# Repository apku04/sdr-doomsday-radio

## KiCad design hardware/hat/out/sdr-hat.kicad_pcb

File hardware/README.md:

# KiCad boards in this folder

Reference only. The owner changed the design on 2026-10-26: the front panel is hand-wired (no panel PCB) and the owner designs the HAT. These scripted KiCad boards (ERC/DRC clean) are kept for reference.

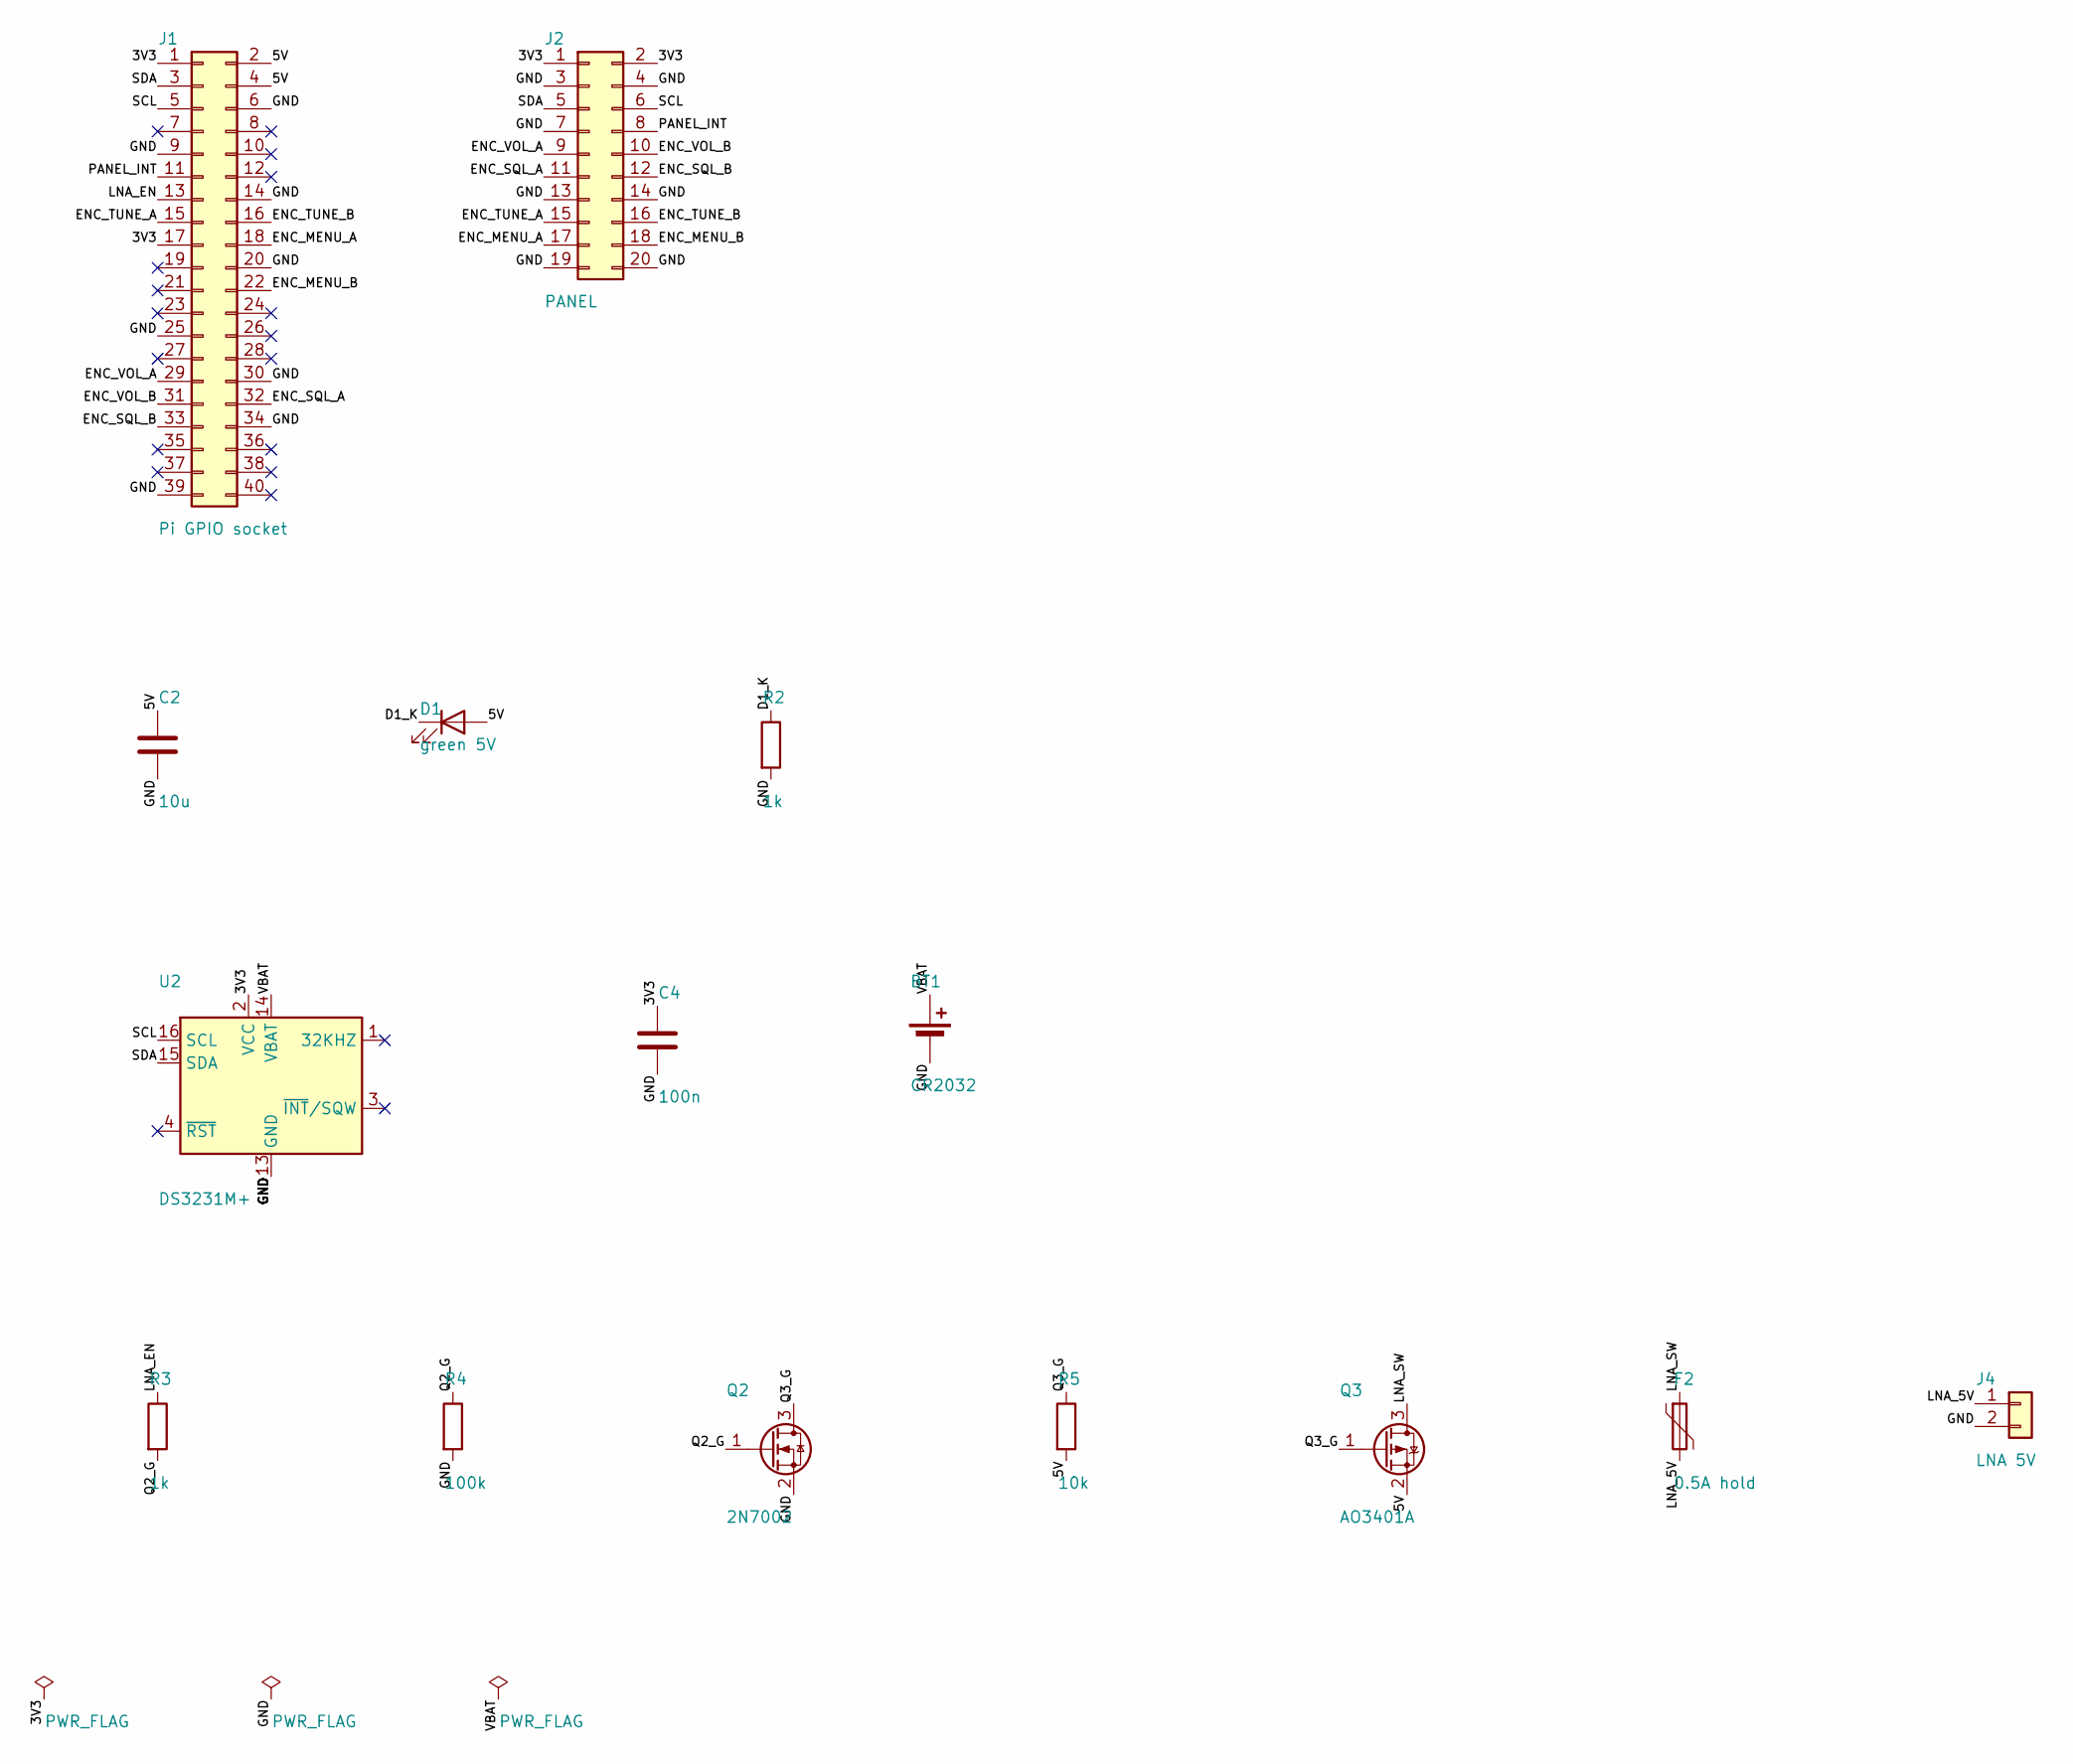
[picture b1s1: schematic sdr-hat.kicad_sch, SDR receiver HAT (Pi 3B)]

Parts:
BT1: CR2032; BatteryHolder_Keystone_3034_1x20mm
C2: 10u; C_0805_2012Metric
C4: 100n; C_0805_2012Metric
D1: green 5V; LED_0805_2012Metric
F2: 0.5A hold; Fuse_1206_3216Metric
J1: Pi GPIO socket; PinSocket_2x20_P2.54mm_Vertical
J2: PANEL; IDC-Header_2x10_P2.54mm_Vertical
J4: LNA 5V; JST_XH_B2B-XH-A_1x02_P2.50mm_Vertical
Q2: 2N7002; SOT-23
Q3: AO3401A; SOT-23
R2, R3: 1k; R_0805_2012Metric
R4: 100k; R_0805_2012Metric
R5: 10k; R_0805_2012Metric
U2: DS3231M+; SOIC-16W_7.5x10.3mm_P1.27mm

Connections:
3V3: C4.1, J1.1, J1.17, J2.1, J2.2, U2.2 (VCC)
5V: C2.1, D1.2 (A), J1.2, J1.4, Q3.2 (S), R5.2
D1_K: D1.1 (K), R2.1
ENC_MENU_A: J1.18, J2.17
ENC_MENU_B: J1.22, J2.18
ENC_SQL_A: J1.32, J2.11
ENC_SQL_B: J1.33, J2.12
ENC_TUNE_A: J1.15, J2.15
ENC_TUNE_B: J1.16, J2.16
ENC_VOL_A: J1.29, J2.9
ENC_VOL_B: J1.31, J2.10
GND: BT1.2 (-), C2.2, C4.2, J1.6, J1.9, J1.14, J1.20, J1.25, J1.30, J1.34, J1.39, J2.3, J2.4, J2.7, J2.13, J2.14, J2.19, J2.20, J4.2, Q2.2 (S), R2.2, R4.2, U2.5 (GND), U2.6 (GND), U2.7 (GND), U2.8 (GND), U2.9 (GND), U2.10 (GND), U2.11 (GND), U2.12 (GND), U2.13 (GND)
LNA_5V: F2.2, J4.1
LNA_EN: J1.13, R3.1
LNA_SW: F2.1, Q3.3 (D)
PANEL_INT: J1.11, J2.8
Q2_G: Q2.1 (G), R3.2, R4.1
Q3_G: Q2.3 (D), Q3.1 (G), R5.1
SCL: J1.5, J2.6, U2.16 (SCL)
SDA: J1.3, J2.5, U2.15 (SDA)
VBAT: BT1.1 (+), U2.14 (VBAT)

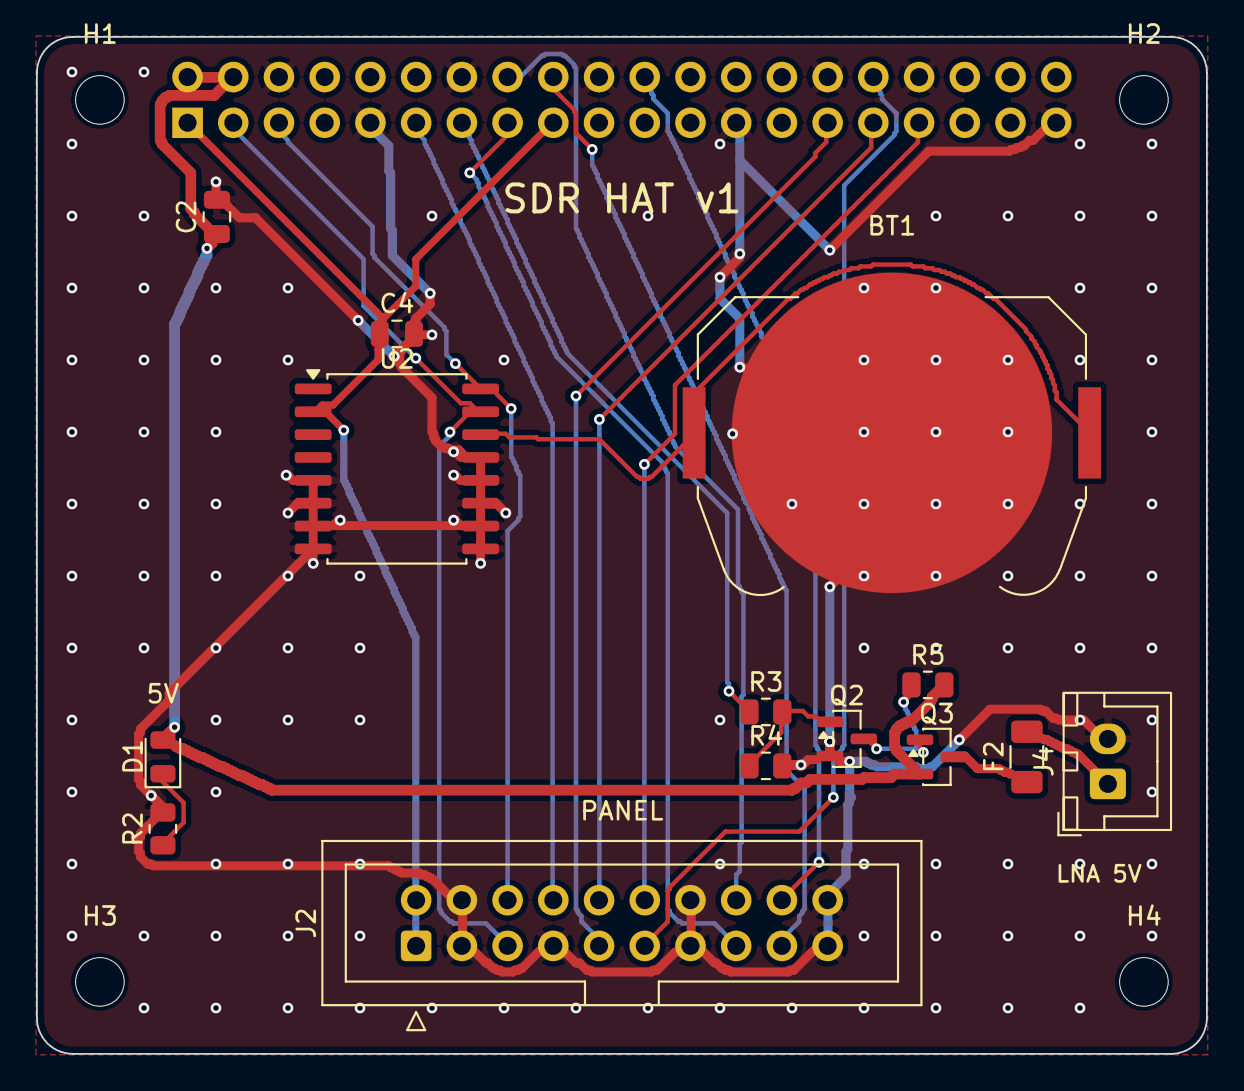
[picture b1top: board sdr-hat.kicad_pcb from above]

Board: 2 copper layers, 65.0 x 56.5 mm, 19 parts (1 on the bottom side), 21 nets.

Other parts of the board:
H1, H2, H3, H4: MountingHole_2.7mm_M2.5

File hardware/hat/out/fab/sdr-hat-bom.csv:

Qty,References,Value,Footprint,LCSC,Note
1,BT1,CR2032,BatteryHolder_Keystone_3034_1x20mm,,Keystone 3034 SMD holder
1,C2,10u,C_0805_2012Metric,,
1,C4,100n,C_0805_2012Metric,,
1,D1,green 5V,LED_0805_2012Metric,,
1,F2,0.5A hold,Fuse_1206_3216Metric,,PTC 1206 0.5 A hold
1,J1,Pi GPIO socket,PinSocket_2x20_P2.54mm_Vertical,,"2x20 female header, 8.5 mm (standard HAT height)"
1,J2,PANEL,IDC-Header_2x10_P2.54mm_Vertical,,"2x10 shrouded box header, keyed"
1,J4,LNA 5V,JST_XH_B2B-XH-A_1x02_P2.50mm_Vertical,,JST-XH 2-pin to back-panel LNA socket
1,Q2,2N7002,SOT-23,,
1,Q3,AO3401A,SOT-23,,
2,R2 R3,1k,R_0805_2012Metric,,
1,R4,100k,R_0805_2012Metric,,
1,R5,10k,R_0805_2012Metric,,
1,U2,DS3231M+,SOIC-16W_7.5x10.3mm_P1.27mm,,"I2C 0x68, MEMS RTC"

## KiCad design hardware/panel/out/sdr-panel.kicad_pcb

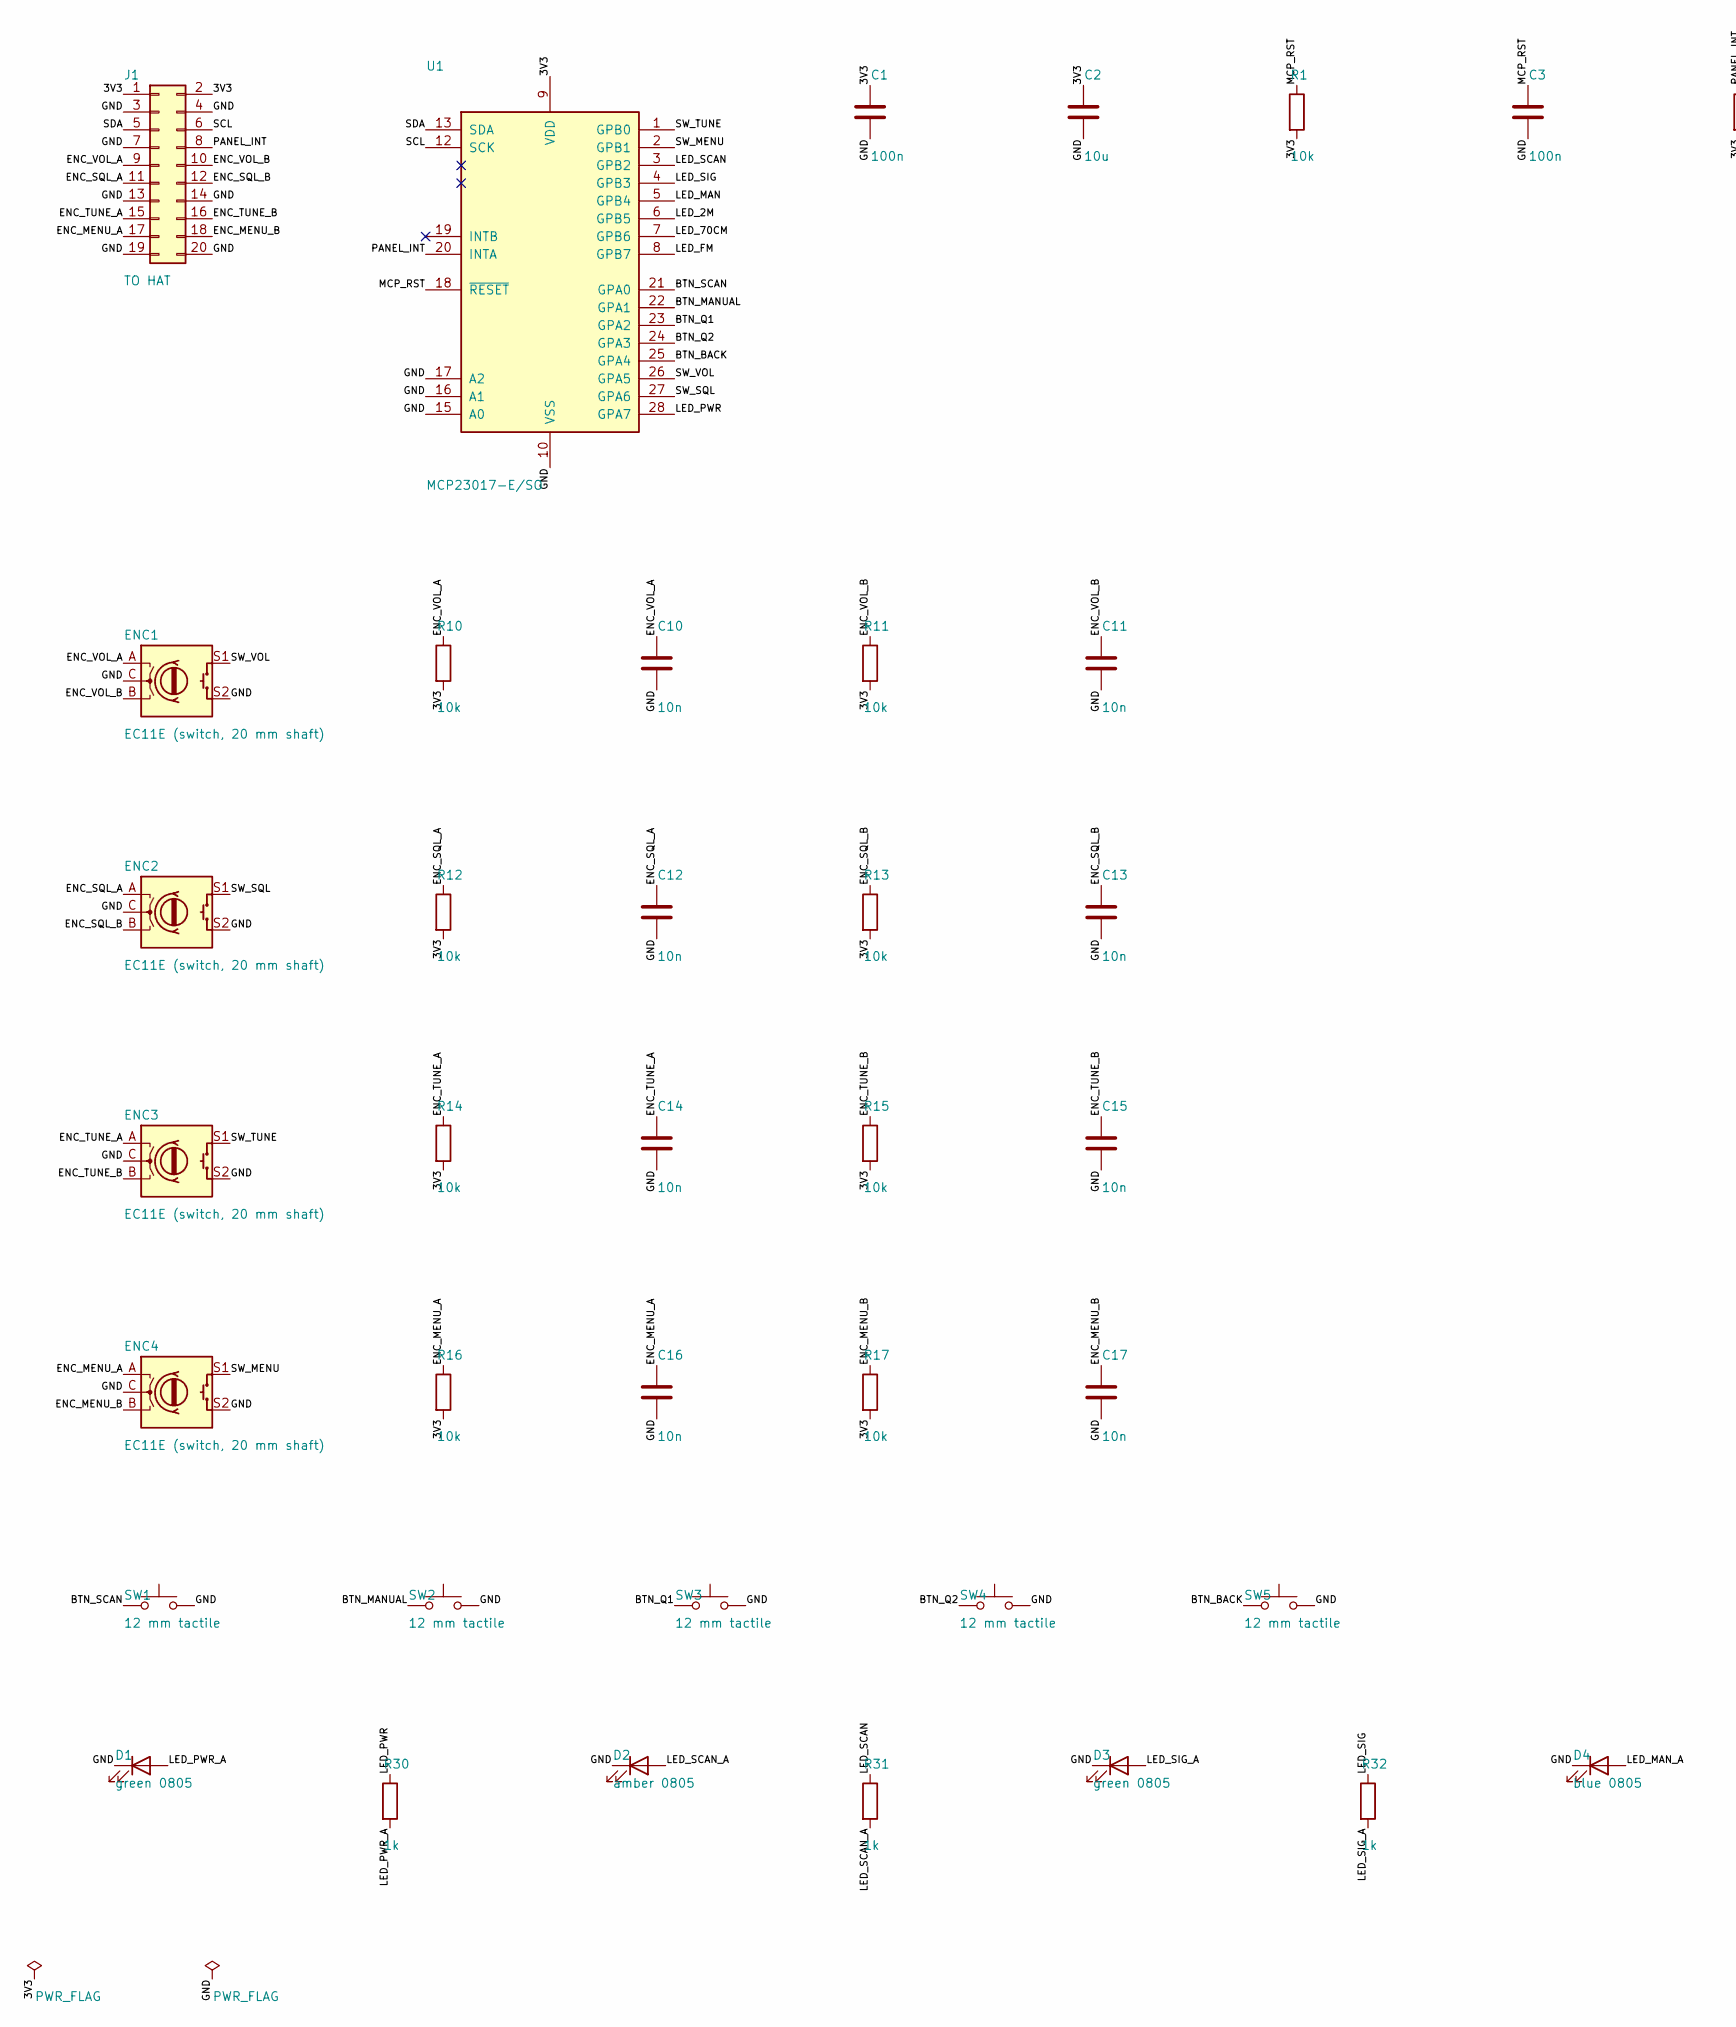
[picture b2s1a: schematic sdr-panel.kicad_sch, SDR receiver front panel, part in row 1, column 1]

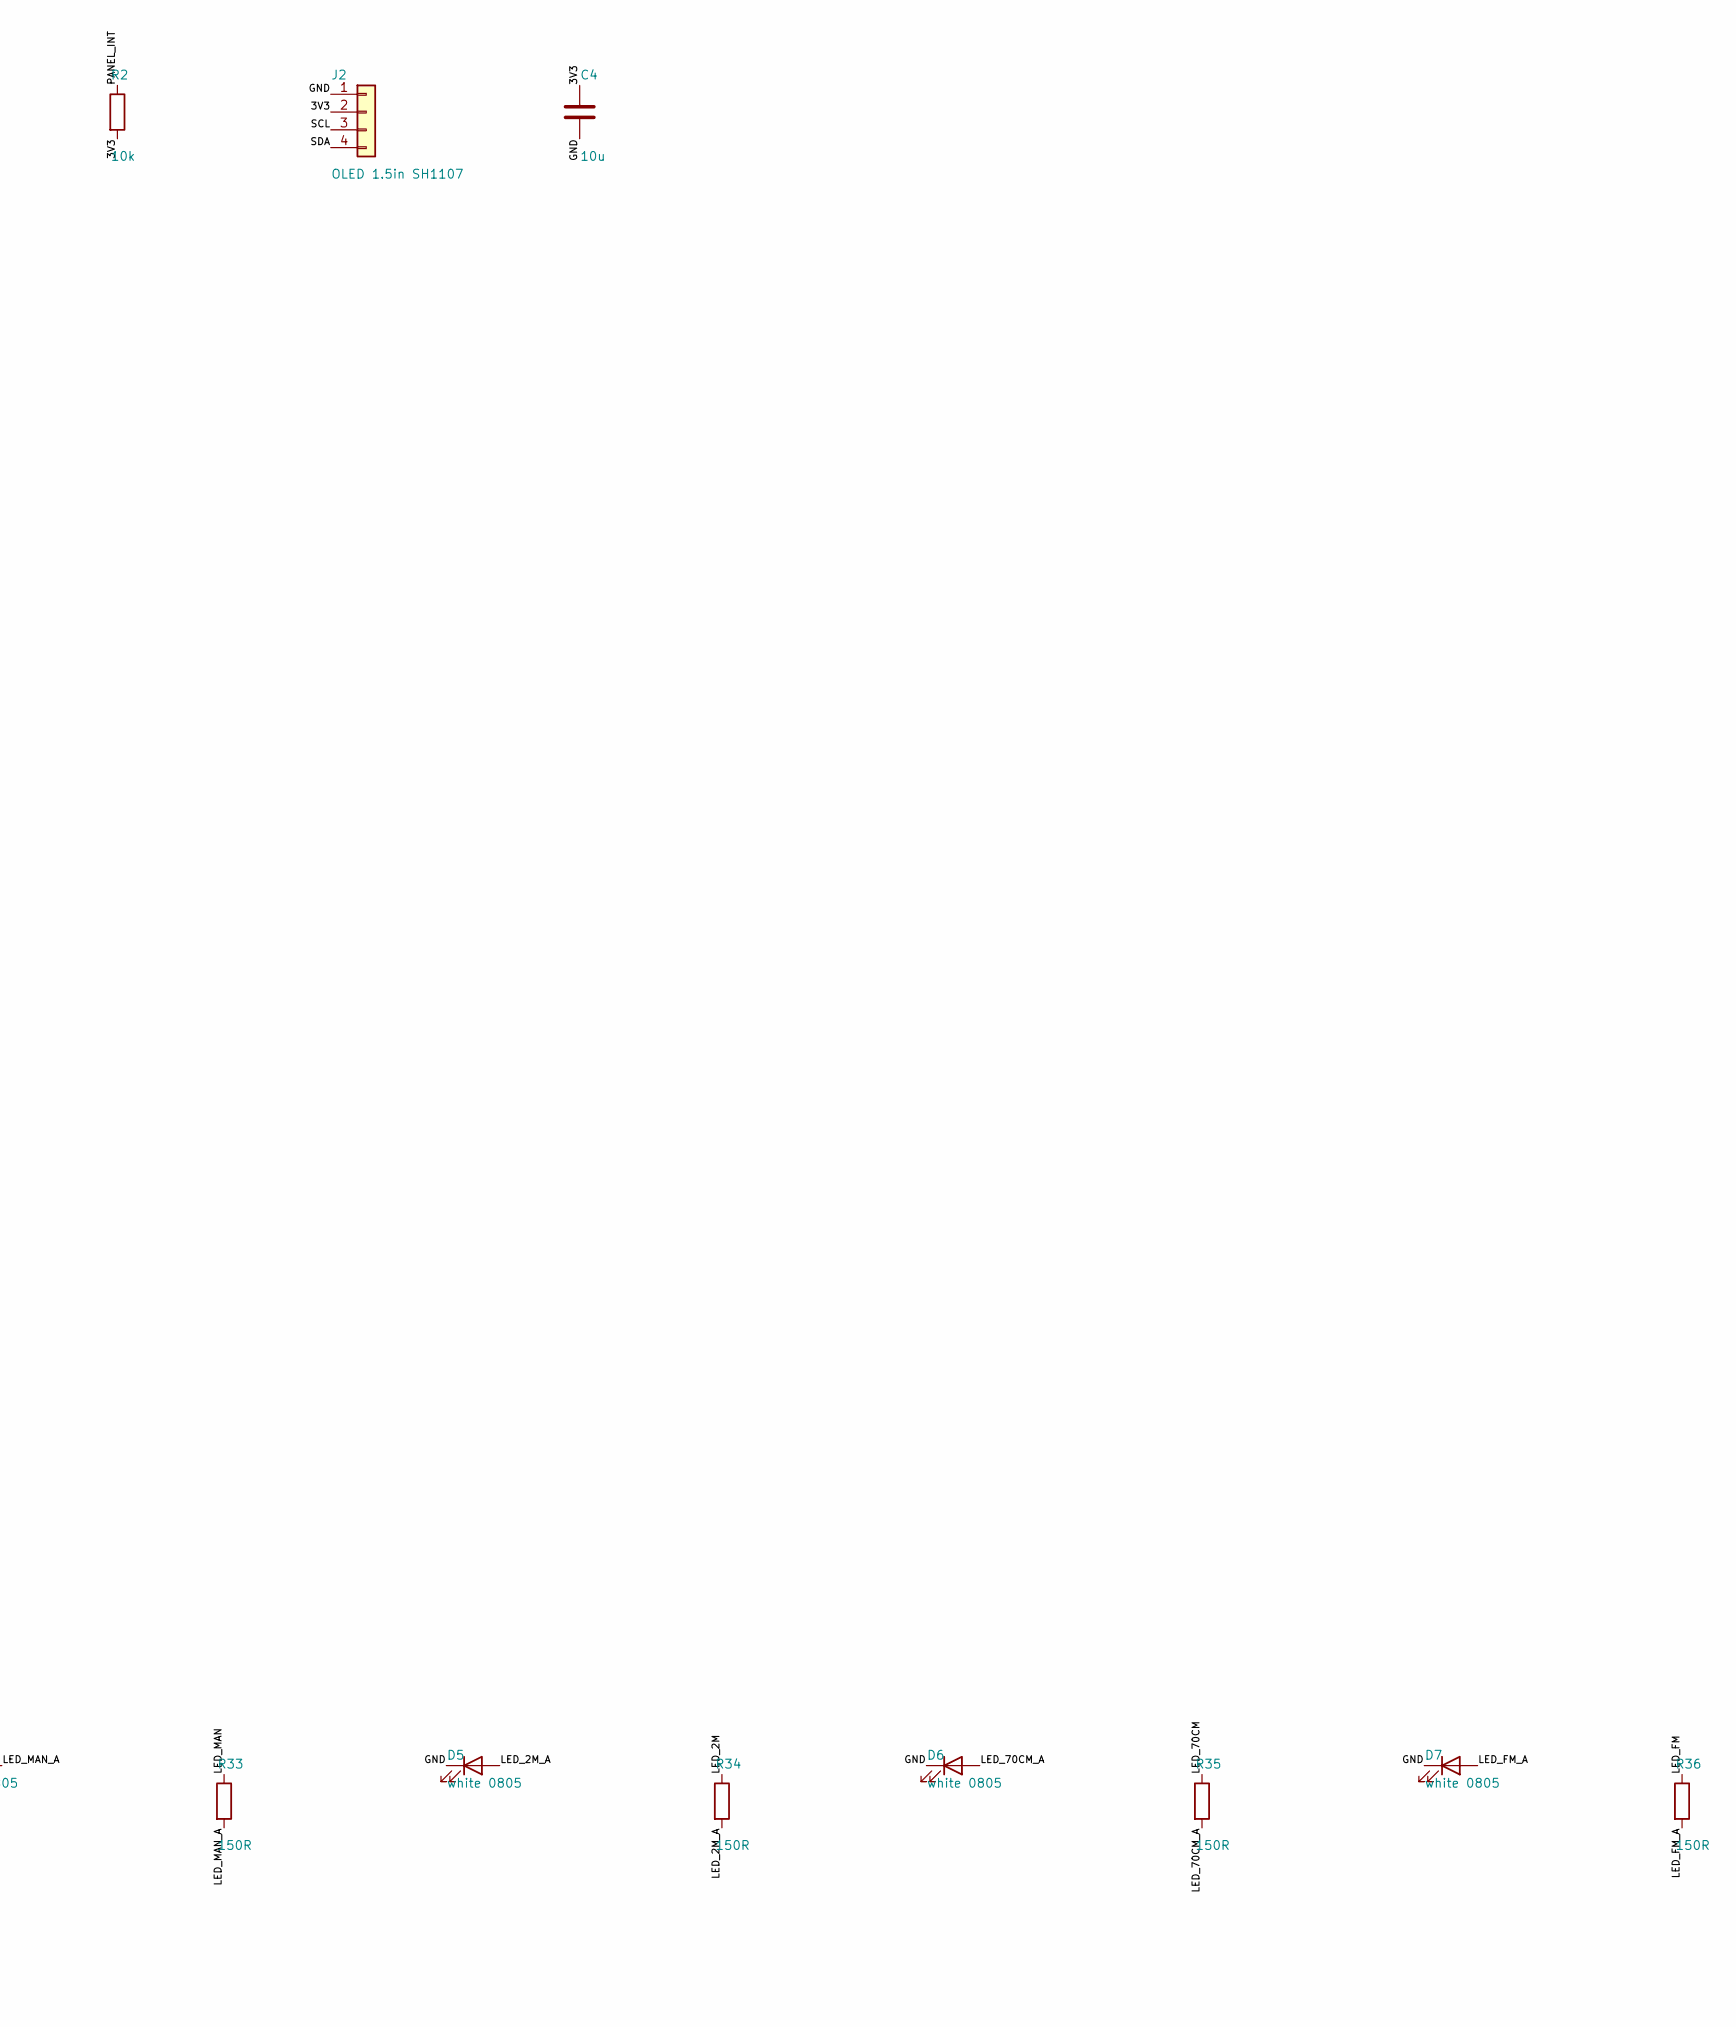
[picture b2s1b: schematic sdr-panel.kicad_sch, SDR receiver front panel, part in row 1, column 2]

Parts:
C1, C3: 100n; C_0805_2012Metric
C2, C4: 10u; C_0805_2012Metric
C10, C11, C12, C13, C14, C15, C16, C17: 10n; C_0805_2012Metric
D1, D3: green 0805; LED_0805_2012Metric
D2: amber 0805; LED_0805_2012Metric
D4: blue 0805; LED_0805_2012Metric
D5, D6, D7: white 0805; LED_0805_2012Metric
ENC1, ENC2, ENC3, ENC4: EC11E (switch, 20 mm shaft); RotaryEncoder_Alps_EC11E-Switch_Vertical_H20mm
J1: TO HAT; IDC-Header_2x10_P2.54mm_Vertical
J2: OLED 1.5in SH1107; PinSocket_1x04_P2.54mm_Vertical
R1, R2, R10, R11, R12, R13, R14, R15, R16, R17: 10k; R_0805_2012Metric
R30, R31, R32: 1k; R_0805_2012Metric
R33, R34, R35, R36: 150R; R_0805_2012Metric
SW1, SW2, SW3, SW4, SW5: 12 mm tactile; SW_PUSH-12mm
U1: MCP23017-E/SO; SOIC-28W_7.5x17.9mm_P1.27mm

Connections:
3V3: C1.1, C2.1, C4.1, J1.1, J1.2, J2.2, R1.2, R2.2, R10.2, R11.2, R12.2, R13.2, R14.2, R15.2, R16.2, R17.2, U1.9 (VDD)
BTN_BACK: SW5.1, U1.25 (GPA4)
BTN_MANUAL: SW2.1, U1.22 (GPA1)
BTN_Q1: SW3.1, U1.23 (GPA2)
BTN_Q2: SW4.1, U1.24 (GPA3)
BTN_SCAN: SW1.1, U1.21 (GPA0)
ENC_MENU_A: C16.1, ENC4.A, J1.17, R16.1
ENC_MENU_B: C17.1, ENC4.B, J1.18, R17.1
ENC_SQL_A: C12.1, ENC2.A, J1.11, R12.1
ENC_SQL_B: C13.1, ENC2.B, J1.12, R13.1
ENC_TUNE_A: C14.1, ENC3.A, J1.15, R14.1
ENC_TUNE_B: C15.1, ENC3.B, J1.16, R15.1
ENC_VOL_A: C10.1, ENC1.A, J1.9, R10.1
ENC_VOL_B: C11.1, ENC1.B, J1.10, R11.1
GND: C1.2, C2.2, C3.2, C4.2, C10.2, C11.2, C12.2, C13.2, C14.2, C15.2, C16.2, C17.2, D1.1 (K), D2.1 (K), D3.1 (K), D4.1 (K), D5.1 (K), D6.1 (K), D7.1 (K), ENC1.C, ENC1.MP, ENC1.S2, ENC2.C, ENC2.MP, ENC2.S2, ENC3.C, ENC3.MP, ENC3.S2, ENC4.C, ENC4.MP, ENC4.S2, J1.3, J1.4, J1.7, J1.13, J1.14, J1.19, J1.20, J2.1, SW1.2, SW2.2, SW3.2, SW4.2, SW5.2, U1.10 (VSS), U1.15 (A0), U1.16 (A1), U1.17 (A2)
LED_2M: R34.1, U1.6 (GPB5)
LED_2M_A: D5.2 (A), R34.2
LED_70CM: R35.1, U1.7 (GPB6)
LED_70CM_A: D6.2 (A), R35.2
LED_FM: R36.1, U1.8 (GPB7)
LED_FM_A: D7.2 (A), R36.2
LED_MAN: R33.1, U1.5 (GPB4)
LED_MAN_A: D4.2 (A), R33.2
LED_PWR: R30.1, U1.28 (GPA7)
LED_PWR_A: D1.2 (A), R30.2
LED_SCAN: R31.1, U1.3 (GPB2)
LED_SCAN_A: D2.2 (A), R31.2
LED_SIG: R32.1, U1.4 (GPB3)
LED_SIG_A: D3.2 (A), R32.2
MCP_RST: C3.1, R1.1, U1.18 (~RESET)
PANEL_INT: J1.8, R2.1, U1.20 (INTA)
SCL: J1.6, J2.3, U1.12 (SCK)
SDA: J1.5, J2.4, U1.13 (SDA)
SW_MENU: ENC4.S1, U1.2 (GPB1)
SW_SQL: ENC2.S1, U1.27 (GPA6)
SW_TUNE: ENC3.S1, U1.1 (GPB0)
SW_VOL: ENC1.S1, U1.26 (GPA5)

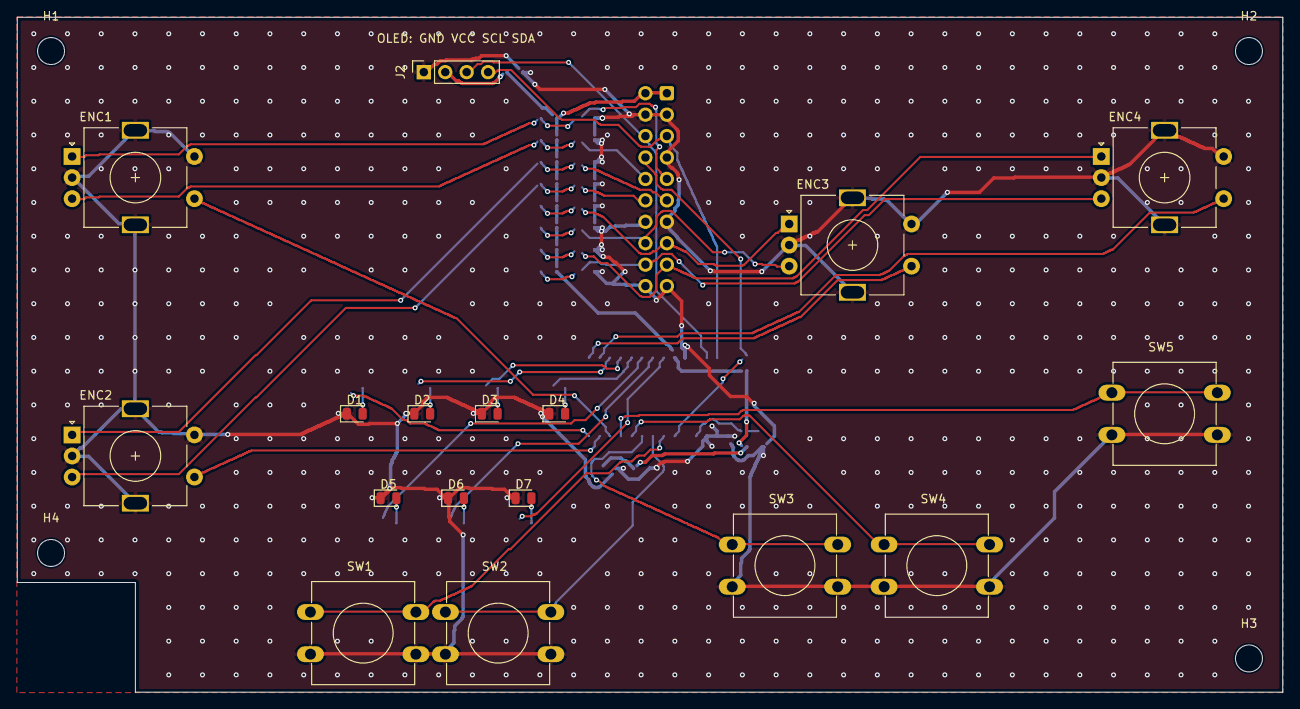
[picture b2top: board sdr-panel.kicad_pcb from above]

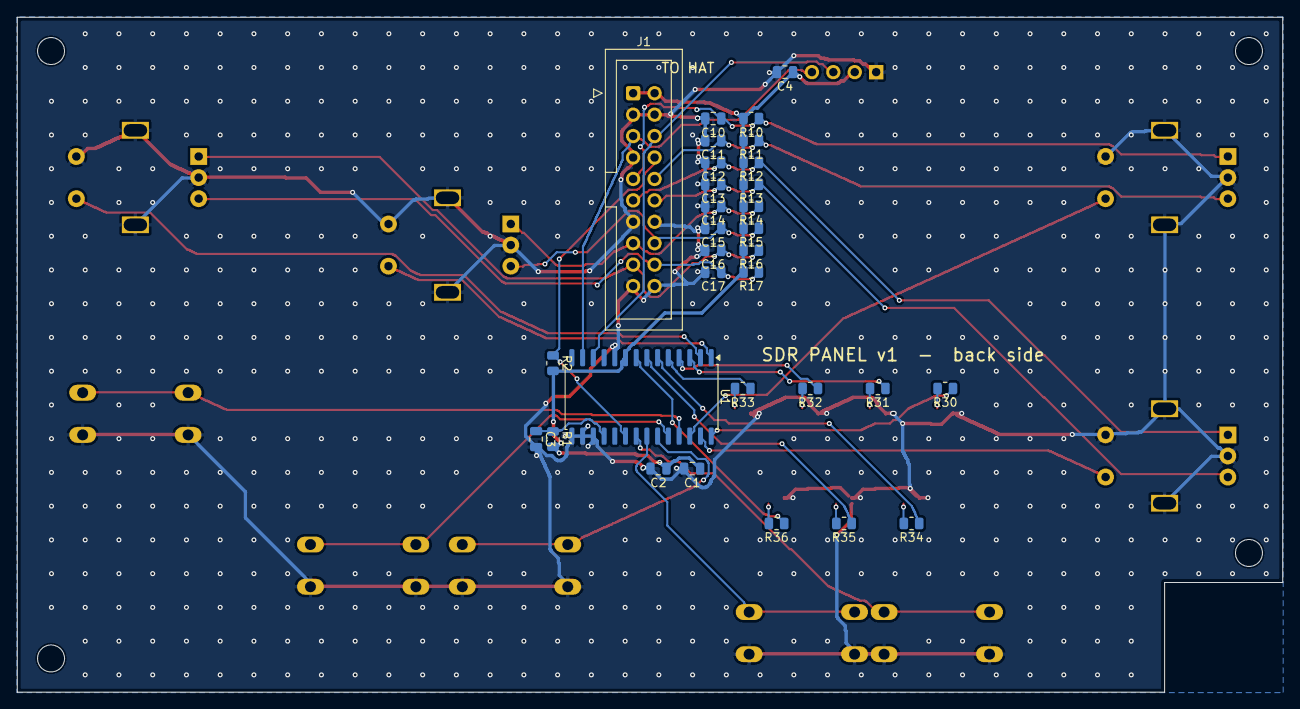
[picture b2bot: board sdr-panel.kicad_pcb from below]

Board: 2 copper layers, 150.0 x 80.0 mm, 52 parts (31 on the bottom side), 37 nets.

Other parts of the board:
H1, H2, H3, H4: MountingHole_3.2mm_M3

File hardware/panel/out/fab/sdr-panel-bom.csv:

Qty,References,Value,Footprint,LCSC,Note
2,C1 C3,100n,C_0805_2012Metric,,
8,C10 C11 C12 C13 C14 C15 C16 C17,10n,C_0805_2012Metric,,
2,C2 C4,10u,C_0805_2012Metric,,
2,D1 D3,green 0805,LED_0805_2012Metric,,
1,D2,amber 0805,LED_0805_2012Metric,,
1,D4,blue 0805,LED_0805_2012Metric,,
3,D5 D6 D7,white 0805,LED_0805_2012Metric,,
4,ENC1 ENC2 ENC3 ENC4,"EC11E (switch, 20 mm shaft)",RotaryEncoder_Alps_EC11E-Switch_Vertical_H20mm,,"EC11 vertical with push switch, M7 bushing"
1,J1,TO HAT,IDC-Header_2x10_P2.54mm_Vertical,,2x10 shrouded box header
1,J2,OLED 1.5in SH1107,PinSocket_1x04_P2.54mm_Vertical,,check module pin order GND VCC SCL SDA before soldering
10,R1 R10 R11 R12 R13 R14 R15 R16 R17 R2,10k,R_0805_2012Metric,,
3,R30 R31 R32,1k,R_0805_2012Metric,,
4,R33 R34 R35 R36,150R,R_0805_2012Metric,,
5,SW1 SW2 SW3 SW4 SW5,12 mm tactile,SW_PUSH-12mm,,"12x12 mm THT tactile, stem height to suit the panel"
1,U1,MCP23017-E/SO,SOIC-28W_7.5x17.9mm_P1.27mm,,I2C 0x20; GPA7/GPB7 used as outputs only
